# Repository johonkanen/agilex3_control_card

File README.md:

# Agilex 3 control card

A small FPGA control card built around an Altera Agilex 3 (A3CZ065BB18AE7S, B18A BGA), designed in KiCad 10. It plugs
into a power-electronics board through a 2×25 1.27 mm header and replaces an older Cyclone 10 card (U25) with the same
outline and connector positions.

| Top | Bottom |
|---|---|
|  |  |

**Status: ready to order (2026-10-28).** The design is complete and fully routed; DRC is clean and the board matches the
schematic. It passed three independent reviews (production files against JLCPCB's capabilities, electrical design, and the
Agilex 3 configuration against Altera's guidelines and two evaluation-kit schematics). After the reviews, the 1.2 V and
HyperRAM 1.8 V LDOs were replaced by bucks and all bucks set to forced PWM (`docs/power_switchers_plan.md`); that change
has not had a separate review. The FPGAs are being bought through
JLCPCB Global Sourcing; the assembly order follows when they reach JLC's warehouse. The board has not been built or tested
yet: `docs/bringup_checklist.md` is the plan for when it arrives.

## Features

- **FPGA:** Agilex 3 A3CZ065, 65k logic elements, speed grade −7, extended temperature. 63 I/O signals, mostly on 3.3 V HVIO
  banks with no level shifters.
- **Memory:** 32 MB HyperRAM (Winbond W958D8NBYA5I, 1.8 V) on bank 6D. The W959D8NFYA5I (64 MB) fits the same footprint.
- **Configuration:** Active Serial x4 from a 1.8 V QSPI flash (Micron MT25QU256). JTAG on a 5-pin 2.54 mm header,
  shifted from 3.3 V to 1.8 V by an SN74AVC4T774.
- **Clock:** 100 MHz 1.8 V oscillator into PLLREFCLK1 (D18) and the configuration clock input OSC_CLK_1.
- **ADC:** 2 channels, each an 8:1 analog mux (SN74LV4051A) → OPA365 buffer → ADS7056 (14-bit, 2.5 MSPS), on a separate
  analog 3.3 V supply.
- **Power:** from 5 V on the header. Every FPGA rail comes from a Diodes AP61x02 buck, all in forced PWM: 0.753 V core
  (with remote sense), 1.8 V, 3.3 V, then 1.2 V and a separate 1.8 V for the HyperRAM bank. They start up in Altera's
  group order, each step enabled by the previous buck's power-good. Only the analog 3.3 V comes from an LDO. The FPGA's
  PLL, ADC and VCCRCORE supplies are filtered with ferrite beads.
- **Indicators:** 2 RGB LEDs.
- **Board:** 32.5 × 33.8 mm, 6 layers, 1.6 mm (JLC stackup JLC06161H-3313), ENIG, 0.65 mm-pitch BGA fanned out with
  filled and capped via-in-pad. 161 parts assembled by JLCPCB on both sides (40 top, 121 bottom); the headers J1 and J2
  are soldered by hand.

## Copper layers

<!-- board-plots:start -->
<!-- Generated by kicad-board-plots; edits between these markers are overwritten. -->

Copper layers of `hardware/control_card.kicad_pcb` in stack order, without silkscreen. Plotted by [kicad-board-plots](https://github.com/johonkanen/kicad-board-plots) on each board change; the images live on the `renders` branch.

<table>
<tr>
<td align="center"><br><b>F.Cu: signal (top)</b></td>
<td align="center"><br><b>In1.Cu: GND plane</b></td>
</tr>
<tr>
<td align="center"><br><b>In2.Cu: signal, +1V8, +1V8_HR, +1V2 pours</b></td>
<td align="center"><br><b>In3.Cu: +0V75, +3V3 planes</b></td>
</tr>
<tr>
<td align="center"><br><b>In4.Cu: GND plane</b></td>
<td align="center"><br><b>B.Cu: signal, GND, +1V2, SW_3V3, SW_1V2, SW_1V8HR and 7 more pours (bottom, mirrored)</b></td>
</tr>
</table>

<!-- board-plots:end -->

## Repository layout

| Path | Contents |
|---|---|
| `hardware/` | KiCad project: schematic (`control_card.kicad_sch` plus `sheets/`), board, design rules (`control_card.kicad_dru` adds JLCPCB limits) |
| `hardware/lib/` | Project symbols and footprints, including the Agilex 3 symbol and the B18A BGA footprint |
| `reference/` | FPGA pin assignment (`pin_assignment.csv`), Altera pin lists, power-board header pinout, JLCPCB part list |
| `docs/` | Design notes, Agilex 3 board requirements, flash requirements, production and bring-up checklists, board renders |
| `tools/` | Python scripts that generated the schematic and board, plus the fabrication-output wrapper |
| `tools/jlc/` | Submodule [jlc-tools](https://github.com/johonkanen/jlc-tools): JLC part search, stock check, BOM/CPL and Gerber export |

## Documentation

- [`docs/design-notes.md`](docs/design-notes.md): architecture, part choices and the reasons for them.
- [`docs/agilex3_requirements.md`](docs/agilex3_requirements.md): what the FPGA needs from the board (supply rails,
  bank voltages, power-up order, configuration pins) and how this card meets each requirement.
- [`docs/agilex_flash_requirements.md`](docs/agilex_flash_requirements.md): configuration flash requirements.
- [`docs/jlcpcb_production_checklist.md`](docs/jlcpcb_production_checklist.md): verifying the design and order files
  against JLCPCB's capabilities, plus the order-form settings.
- [`docs/bringup_checklist.md`](docs/bringup_checklist.md): testing the assembled boards, from inspection and first
  power-up to configuration, HyperRAM, ADCs and the power-board interface.
- [`docs/order_checklist.md`](docs/order_checklist.md): the earlier hand-off list from routing to ordering (history).

## Opening the design

Clone with `git clone --recursive`, or run `git submodule update --init` after cloning, to get `tools/jlc`.

Open `hardware/control_card.kicad_pro` in KiCad 10. The project's own symbol and footprint libraries are set up in
`hardware/sym-lib-table` and `hardware/fp-lib-table`. Everything else comes from KiCad's standard libraries.

## Fabrication outputs

```sh
KICAD_ROOT=<unpacked KiCad AppImage (squashfs-root)> tools/fab_outputs.sh
```

This writes `hardware/fab/`:
- Gerbers and drill files, zipped;
- the JLCPCB BOM and placement files;
- a DRC report.

The headers J1 and J2 are left out of the assembly files, because they are soldered by hand. The FPGA has no JLCPCB
part number, so order it through JLCPCB's Global Sourcing or supply it yourself. Global Sourcing parts can only be used
in an assembly order once they have arrived in JLC's warehouse (Parts Manager → My Parts Lib).

Check stock right before ordering: judge each part by JLC's orderable quantity and minimum purchase, not the plain stock
count (see the production checklist, section 5):

```sh
python3 -I tools/jlc/stock_check.py hardware/fab/bom_jlcpcb.csv --boards 10
```

## FPGA pin assignment

`reference/pin_assignment.csv` lists every used FPGA ball with its signal, bank, direction and pin function, generated
from the schematic netlist. Quartus settings:
- banks 6C and 6D: 1.8-V LVCMOS;
- other banks: 3.3-V LVCMOS;
- configuration scheme: Active Serial x4;
- `DEVICE_INITIALIZATION_CLOCK OSC_CLK_1_100MHZ`;
- `ACTIVE_SERIAL_CLOCK AS_FREQ_100MHZ`.

## Generator scripts

The initial schematic and board came from the scripts in `tools/`:
- `gen_schematic.py` writes the schematic;
- `build_pcb.sh` builds the board: placement, FPGA pin assignment, power copper and routing.

The design has since been edited by hand in KiCad, so **don't rerun `gen_schematic.py` or `build_pcb.sh` on this
version**: they would overwrite the hand edits, pin swaps and routing. They stay in the repository as a record of how
the design was made.

## License

[MIT](LICENSE).

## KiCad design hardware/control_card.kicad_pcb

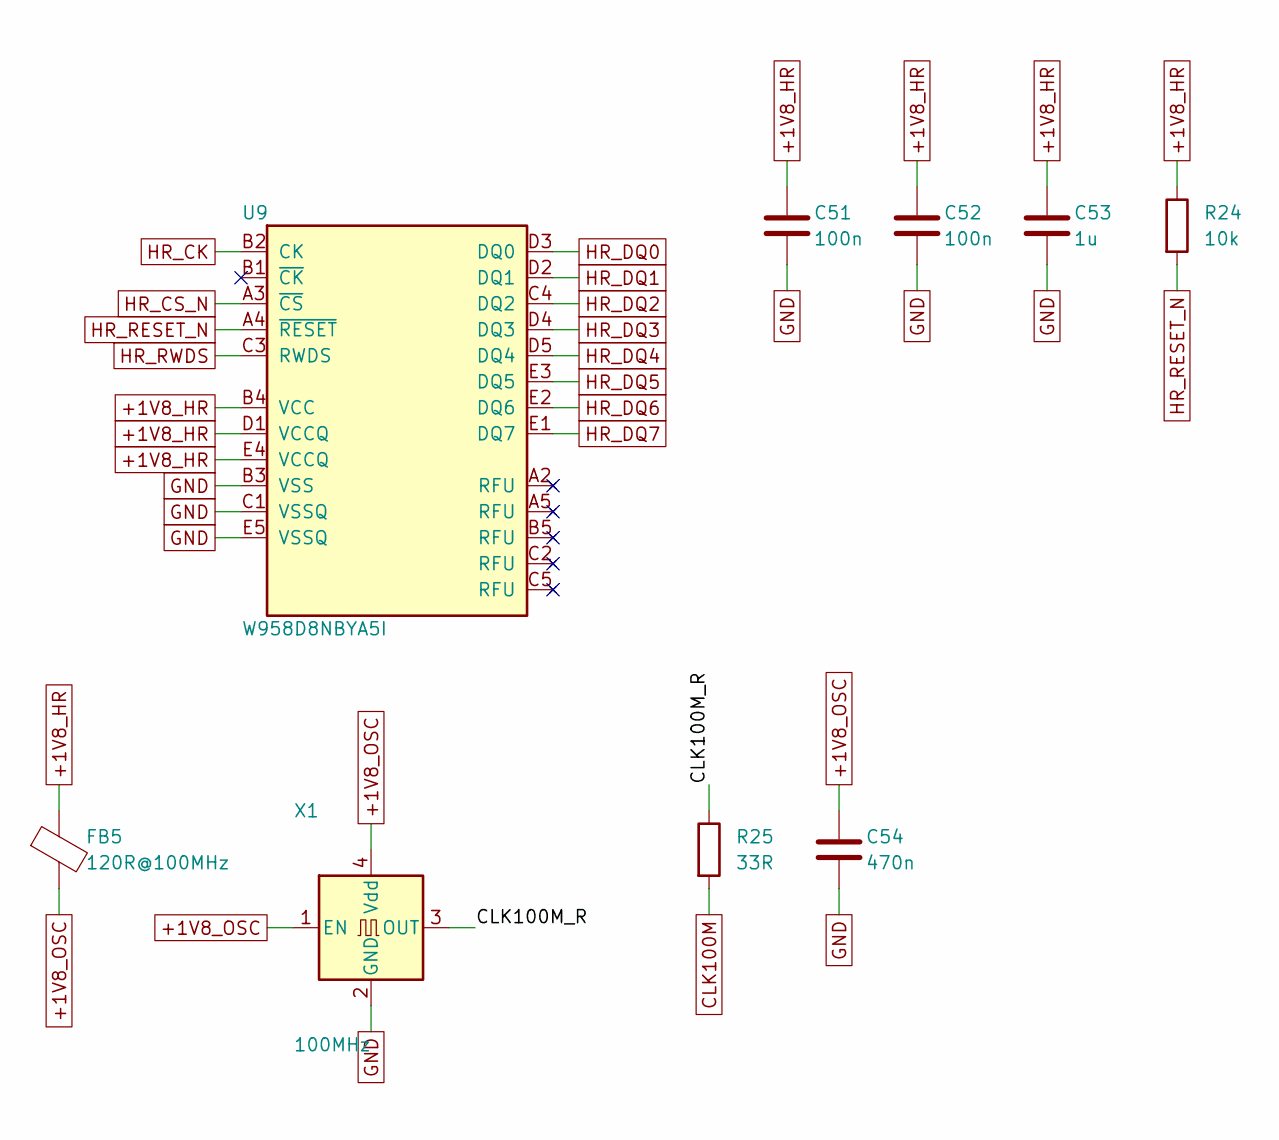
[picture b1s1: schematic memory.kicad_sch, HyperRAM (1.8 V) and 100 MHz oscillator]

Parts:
C51, C52: 100n; C_0402_1005Metric; MPN CL05B104KO5NNNC; LCSC C1525
C53: 1u; C_0402_1005Metric; MPN CL05A105KA5NQNC; LCSC C52923
C54: 470n; C_0402_1005Metric; MPN CL05A474KP5NNNC; LCSC C47339
FB5: 120R@100MHz; L_0603_1608Metric; MPN BLM18PG121SN1D; LCSC C14709
R24: 10k; R_0402_1005Metric; MPN 0402WGF1002TCE; LCSC C25744
R25: 33R; R_0402_1005Metric; MPN 0402WGF330JTCE; LCSC C25105
U9: W958D8NBYA5I; BGA-24_6x8mm_Layout5x5_P1.0mm_CY0.5; MPN W958D8NBYA5I; LCSC C7420405
X1: 100MHz; Oscillator_SMD_Abracon_ASE-4Pin_3.2x2.5mm; MPN OT3225100MJBA4SL; LCSC C4353707

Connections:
+1V8_HR: C51.1, C52.1, C53.1, FB5.1, R24.1, U9.B4 (VCC), U9.D1 (VCCQ), U9.E4 (VCCQ); also elsewhere on the board
+1V8_OSC: C54.1, FB5.2, X1.1 (EN), X1.4 (Vdd)
/HyperRAM and clock/CLK100M_R: R25.1, X1.3 (OUT)
CLK100M: R25.2; also elsewhere on the board
GND: C51.2, C52.2, C53.2, C54.2, U9.B3 (VSS), U9.C1 (VSSQ), U9.E5 (VSSQ), X1.2 (GND); also elsewhere on the board
HR_CK: U9.B2 (CK); also elsewhere on the board
HR_CS_N: U9.A3 (~CS); also elsewhere on the board
HR_DQ0: U9.D3 (DQ0); also elsewhere on the board
HR_DQ1: U9.D2 (DQ1); also elsewhere on the board
HR_DQ2: U9.C4 (DQ2); also elsewhere on the board
HR_DQ3: U9.D4 (DQ3); also elsewhere on the board
HR_DQ4: U9.D5 (DQ4); also elsewhere on the board
HR_DQ5: U9.E3 (DQ5); also elsewhere on the board
HR_DQ6: U9.E2 (DQ6); also elsewhere on the board
HR_DQ7: U9.E1 (DQ7); also elsewhere on the board
HR_RESET_N: R24.2, U9.A4 (~RESET); also elsewhere on the board
HR_RWDS: U9.C3 (RWDS); also elsewhere on the board

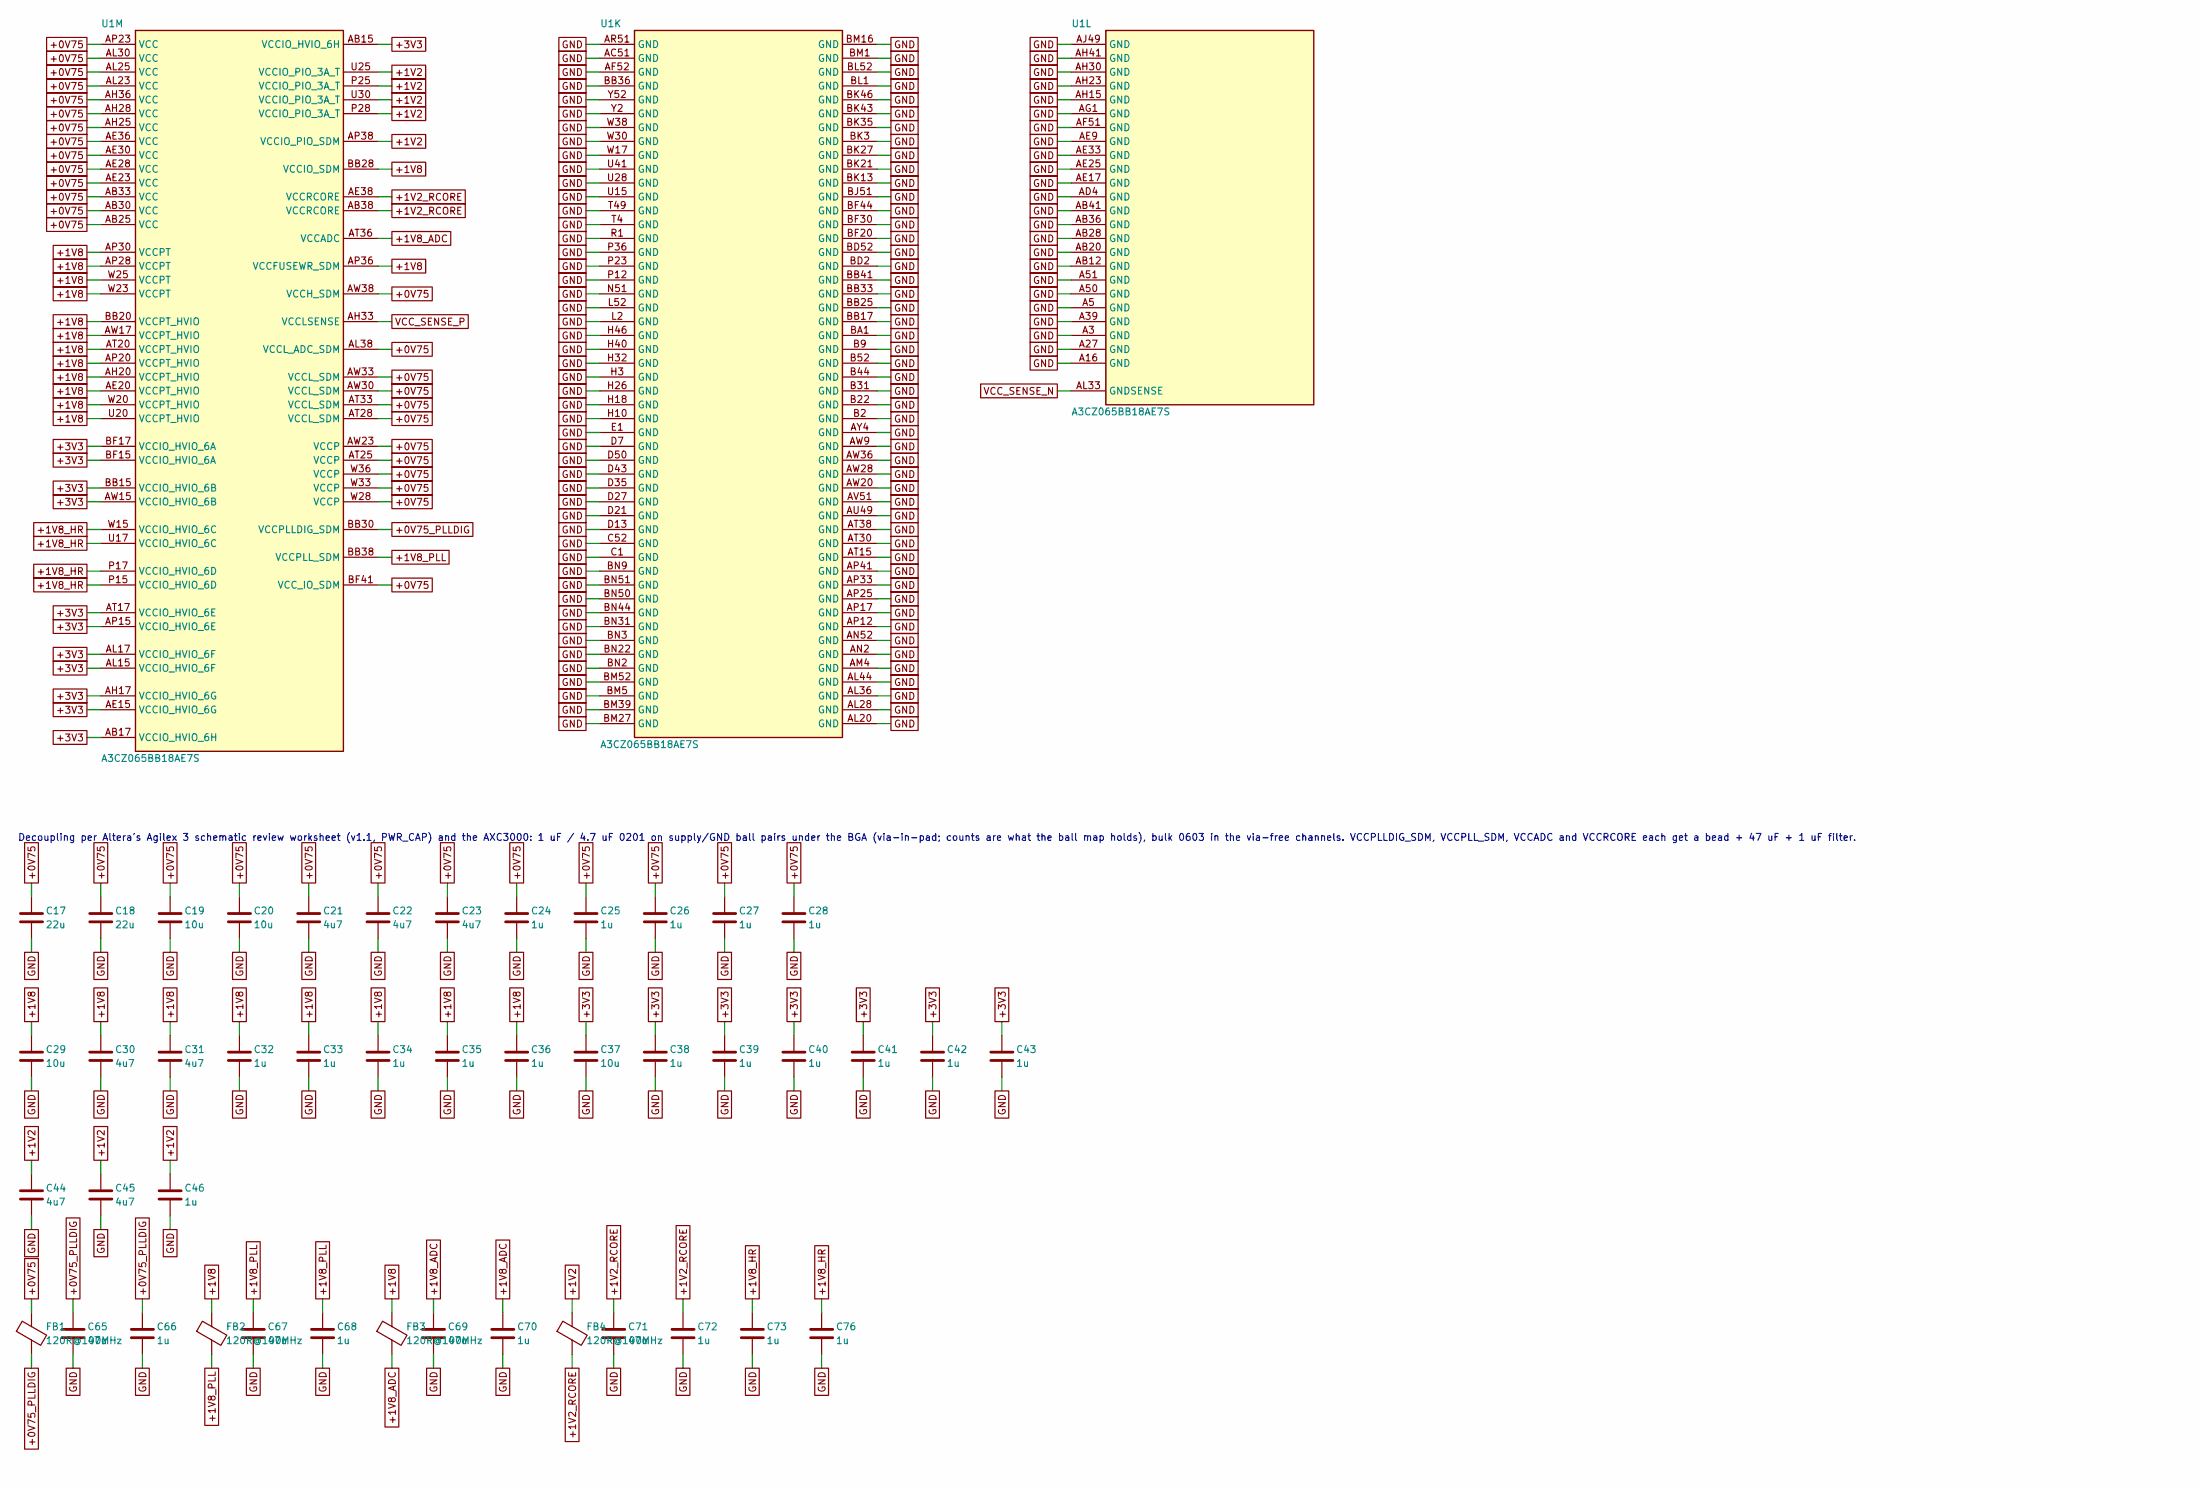
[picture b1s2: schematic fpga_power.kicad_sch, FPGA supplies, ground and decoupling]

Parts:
C17, C18: 22u; C_0603_1608Metric; MPN CL10A226MQ8NRNC; LCSC C59461
C19, C20, C29, C37: 10u; C_0603_1608Metric; MPN CL10A106KP8NNNC; LCSC C19702
C21, C22, C23, C30, C31, C45: 4u7; C_0201_0603Metric; MPN JDK063BBJ475MV-AT; LCSC C2880368
C24, C25, C26, C27, C28, C32, C33, C34, C35, C36, C38, C39, C40, C41, C42, C43, C46, C66, C68, C70, C72, C73, C76: 1u; C_0201_0603Metric; MPN CL03A105MQ3CSNC; LCSC C170152
C44: 4u7; C_0603_1608Metric; MPN CL10A475KO8NNNC; LCSC C19666
C65, C67, C69, C71: 47u; C_0603_1608Metric; MPN GRM188R60J476ME15D; LCSC C140782
FB1, FB2, FB3, FB4: 120R@100MHz; L_0603_1608Metric; MPN BLM18PG121SN1D; LCSC C14709
U1: A3CZ065BB18AE7S; Altera_B18A; MPN A3CZ065BB18AE7S

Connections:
+0V75: C17.1, C18.1, C19.1, C20.1, C21.1, C22.1, C23.1, C24.1, C25.1, C26.1, C27.1, C28.1, FB1.1, U1.AB25 (VCC), U1.AB30 (VCC), U1.AB33 (VCC), U1.AE23 (VCC), U1.AE28 (VCC), U1.AE30 (VCC), U1.AE36 (VCC), U1.AH25 (VCC), U1.AH28 (VCC), U1.AH36 (VCC), U1.AL23 (VCC), U1.AL25 (VCC), U1.AL30 (VCC), U1.AL38 (VCCL_ADC_SDM), U1.AP23 (VCC), U1.AT25 (VCCP), U1.AT28 (VCCL_SDM), U1.AT33 (VCCL_SDM), U1.AW23 (VCCP), U1.AW30 (VCCL_SDM), U1.AW33 (VCCL_SDM), U1.AW38 (VCCH_SDM), U1.BF41 (VCC_IO_SDM), U1.W28 (VCCP), U1.W33 (VCCP), U1.W36 (VCCP); also elsewhere on the board
+0V75_PLLDIG: C65.1, C66.1, FB1.2, U1.BB30 (VCCPLLDIG_SDM)
+1V2: C44.1, C45.1, C46.1, FB4.1, U1.AP38 (VCCIO_PIO_SDM), U1.P25 (VCCIO_PIO_3A_T), U1.P28 (VCCIO_PIO_3A_T), U1.U25 (VCCIO_PIO_3A_T), U1.U30 (VCCIO_PIO_3A_T); also elsewhere on the board
+1V2_RCORE: C71.1, C72.1, FB4.2, U1.AB38 (VCCRCORE), U1.AE38 (VCCRCORE)
+1V8: C29.1, C30.1, C31.1, C32.1, C33.1, C34.1, C35.1, C36.1, FB2.1, FB3.1, U1.AE20 (VCCPT_HVIO), U1.AH20 (VCCPT_HVIO), U1.AP20 (VCCPT_HVIO), U1.AP28 (VCCPT), U1.AP30 (VCCPT), U1.AP36 (VCCFUSEWR_SDM), U1.AT20 (VCCPT_HVIO), U1.AW17 (VCCPT_HVIO), U1.BB20 (VCCPT_HVIO), U1.BB28 (VCCIO_SDM), U1.U20 (VCCPT_HVIO), U1.W20 (VCCPT_HVIO), U1.W23 (VCCPT), U1.W25 (VCCPT); also elsewhere on the board
+1V8_ADC: C69.1, C70.1, FB3.2, U1.AT36 (VCCADC)
+1V8_HR: C73.1, C76.1, U1.P15 (VCCIO_HVIO_6D), U1.P17 (VCCIO_HVIO_6D), U1.U17 (VCCIO_HVIO_6C), U1.W15 (VCCIO_HVIO_6C); also elsewhere on the board
+1V8_PLL: C67.1, C68.1, FB2.2, U1.BB38 (VCCPLL_SDM)
+3V3: C37.1, C38.1, C39.1, C40.1, C41.1, C42.1, C43.1, U1.AB15 (VCCIO_HVIO_6H), U1.AB17 (VCCIO_HVIO_6H), U1.AE15 (VCCIO_HVIO_6G), U1.AH17 (VCCIO_HVIO_6G), U1.AL15 (VCCIO_HVIO_6F), U1.AL17 (VCCIO_HVIO_6F), U1.AP15 (VCCIO_HVIO_6E), U1.AT17 (VCCIO_HVIO_6E), U1.AW15 (VCCIO_HVIO_6B), U1.BB15 (VCCIO_HVIO_6B), U1.BF15 (VCCIO_HVIO_6A), U1.BF17 (VCCIO_HVIO_6A); also elsewhere on the board
GND: C17.2, C18.2, C19.2, C20.2, C21.2, C22.2, C23.2, C24.2, C25.2, C26.2, C27.2, C28.2, C29.2, C30.2, C31.2, C32.2, C33.2, C34.2, C35.2, C36.2, C37.2, C38.2, C39.2, C40.2, C41.2, C42.2, C43.2, C44.2, C45.2, C46.2, C65.2, C66.2, C67.2, C68.2, C69.2, C70.2, C71.2, C72.2, C73.2, C76.2, U1.A3 (GND), U1.A5 (GND), U1.A16 (GND), U1.A27 (GND), U1.A39 (GND), U1.A50 (GND), U1.A51 (GND), U1.AB12 (GND), U1.AB20 (GND), U1.AB28 (GND), U1.AB36 (GND), U1.AB41 (GND), U1.AC51 (GND), U1.AD4 (GND), U1.AE9 (GND), U1.AE17 (GND), U1.AE25 (GND), U1.AE33 (GND), U1.AF51 (GND), U1.AF52 (GND), U1.AG1 (GND), U1.AH15 (GND), U1.AH23 (GND), U1.AH30 (GND), U1.AH41 (GND), U1.AJ49 (GND), U1.AL20 (GND), U1.AL28 (GND), U1.AL36 (GND), U1.AL44 (GND), U1.AM4 (GND), U1.AN2 (GND), U1.AN52 (GND), U1.AP12 (GND), U1.AP17 (GND), U1.AP25 (GND), U1.AP33 (GND), U1.AP41 (GND), U1.AR51 (GND), U1.AT15 (GND), U1.AT30 (GND), U1.AT38 (GND), U1.AU49 (GND), U1.AV51 (GND), U1.AW9 (GND), U1.AW20 (GND), U1.AW28 (GND), U1.AW36 (GND), U1.AY4 (GND), U1.B2 (GND), U1.B9 (GND), U1.B22 (GND), U1.B31 (GND), U1.B44 (GND), U1.B52 (GND), U1.BA1 (GND), U1.BB17 (GND), U1.BB25 (GND), U1.BB33 (GND), U1.BB36 (GND), U1.BB41 (GND), U1.BD2 (GND), U1.BD52 (GND), U1.BF20 (GND), U1.BF30 (GND), U1.BF44 (GND), U1.BJ51 (GND), U1.BK3 (GND), U1.BK13 (GND), U1.BK21 (GND), U1.BK27 (GND), U1.BK35 (GND), U1.BK43 (GND), U1.BK46 (GND), U1.BL1 (GND), U1.BL52 (GND), U1.BM1 (GND), U1.BM5 (GND), U1.BM16 (GND), U1.BM27 (GND), U1.BM39 (GND), U1.BM52 (GND), U1.BN2 (GND), U1.BN3 (GND), U1.BN9 (GND), U1.BN22 (GND), U1.BN31 (GND), U1.BN44 (GND), U1.BN50 (GND), U1.BN51 (GND), U1.C1 (GND), U1.C52 (GND), U1.D7 (GND), U1.D13 (GND), U1.D21 (GND), U1.D27 (GND), U1.D35 (GND), U1.D43 (GND), U1.D50 (GND), U1.E1 (GND), U1.H3 (GND), U1.H10 (GND), U1.H18 (GND), U1.H26 (GND), U1.H32 (GND), U1.H40 (GND), U1.H46 (GND), U1.L2 (GND), U1.L52 (GND), U1.N51 (GND), U1.P12 (GND), U1.P23 (GND), U1.P36 (GND), U1.R1 (GND), U1.T4 (GND), U1.T49 (GND), U1.U15 (GND), U1.U28 (GND), U1.U41 (GND), U1.W17 (GND), U1.W30 (GND), U1.W38 (GND), U1.Y2 (GND), U1.Y52 (GND); also elsewhere on the board
VCC_SENSE_N: U1.AL33 (GNDSENSE); also elsewhere on the board
VCC_SENSE_P: U1.AH33 (VCCLSENSE); also elsewhere on the board

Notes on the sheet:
Decoupling per Altera's Agilex 3 schematic review worksheet (v1.1, PWR_CAP) and the AXC3000: 1 uF / 4.7 uF 0201 on supply/GND ball pairs under the BGA (via-in-pad; counts are what the ball map holds), bulk 0603 in the via-free channels. VCCPLLDIG_SDM, VCCPLL_SDM, VCCADC and VCCRCORE each get a bead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

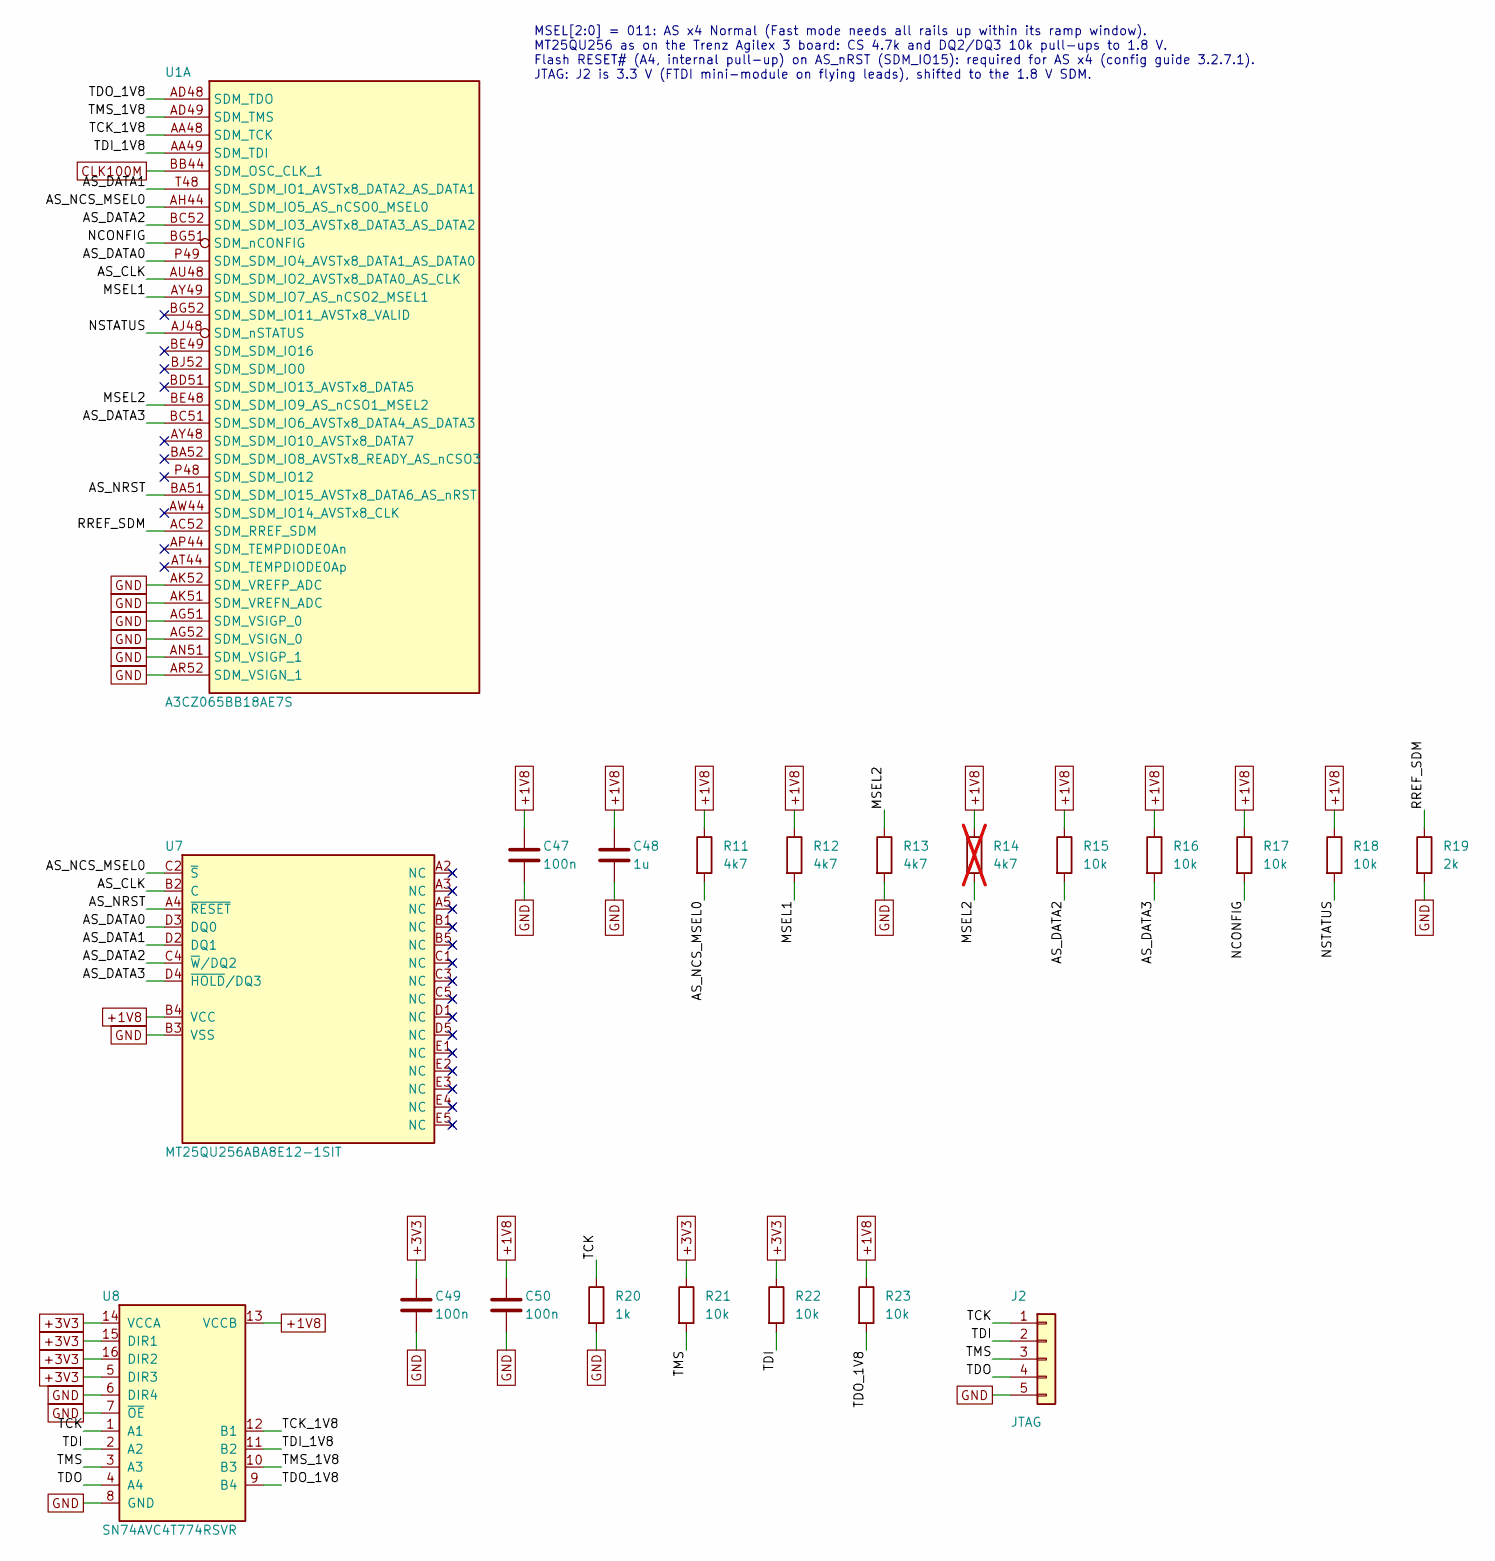
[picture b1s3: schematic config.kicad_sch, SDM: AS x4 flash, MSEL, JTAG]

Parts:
C47: 100n; C_0402_1005Metric; MPN CL05B104KO5NNNC; LCSC C1525
C48: 1u; C_0402_1005Metric; MPN CL05A105KA5NQNC; LCSC C52923
C49, C50: 100n; C_0201_0603Metric; MPN CL03A104KP3NNNC; LCSC C49062
J2: JTAG; PinHeader_1x05_P2.54mm_Vertical
R11, R12, R13: 4k7; R_0402_1005Metric; MPN 0402WGF4701TCE; LCSC C25900
R14: 4k7; R_0402_1005Metric; MPN 0402WGF4701TCE; LCSC C25900; not fitted
R15, R16, R17, R18: 10k; R_0402_1005Metric; MPN 0402WGF1002TCE; LCSC C25744
R19: 2k; R_0402_1005Metric; MPN 0402WGF2001TCE; LCSC C4109
R20: 1k; R_0201_0603Metric; MPN 0201WMF1001TEE; LCSC C270365
R21, R22, R23: 10k; R_0201_0603Metric; MPN 0201WMF1002TEE; LCSC C473048
U1: A3CZ065BB18AE7S; Altera_B18A; MPN A3CZ065BB18AE7S
U7: MT25QU256ABA8E12-1SIT; BGA-24_6x8mm_Layout5x5_P1.0mm_CY0.5; MPN MT25QU256ABA8E12-1SIT; LCSC C2061023
U8: SN74AVC4T774RSVR; UQFN-16_1.8x2.6mm_P0.4mm; MPN SN74AVC4T774RSVR; LCSC C779392

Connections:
+1V8: C47.1, C48.1, C50.1, R11.1, R12.1, R14.1, R15.1, R16.1, R17.1, R18.1, R23.1, U7.B4 (VCC), U8.13 (VCCB); also elsewhere on the board
+3V3: C49.1, R21.1, R22.1, U8.5 (DIR3), U8.14 (VCCA), U8.15 (DIR1), U8.16 (DIR2); also elsewhere on the board
/Configuration/AS_CLK: U1.AU48 (SDM_SDM_IO2_AVSTx8_DATA0_AS_CLK), U7.B2 (C)
/Configuration/AS_DATA0: U1.P49 (SDM_SDM_IO4_AVSTx8_DATA1_AS_DATA0), U7.D3 (DQ0)
/Configuration/AS_DATA1: U1.T48 (SDM_SDM_IO1_AVSTx8_DATA2_AS_DATA1), U7.D2 (DQ1)
/Configuration/AS_DATA2: R15.2, U1.BC52 (SDM_SDM_IO3_AVSTx8_DATA3_AS_DATA2), U7.C4 (~W/DQ2)
/Configuration/AS_DATA3: R16.2, U1.BC51 (SDM_SDM_IO6_AVSTx8_DATA4_AS_DATA3), U7.D4 (~HOLD/DQ3)
/Configuration/AS_NCS_MSEL0: R11.2, U1.AH44 (SDM_SDM_IO5_AS_nCSO0_MSEL0), U7.C2 (~S)
/Configuration/AS_NRST: U1.BA51 (SDM_SDM_IO15_AVSTx8_DATA6_AS_nRST), U7.A4 (~RESET)
/Configuration/MSEL1: R12.2, U1.AY49 (SDM_SDM_IO7_AS_nCSO2_MSEL1)
/Configuration/MSEL2: R13.1, R14.2, U1.BE48 (SDM_SDM_IO9_AS_nCSO1_MSEL2)
/Configuration/NCONFIG: R17.2, U1.BG51 (SDM_nCONFIG)
/Configuration/NSTATUS: R18.2, U1.AJ48 (SDM_nSTATUS)
/Configuration/RREF_SDM: R19.1, U1.AC52 (SDM_RREF_SDM)
/Configuration/TCK: J2.1, R20.1, U8.1 (A1)
/Configuration/TCK_1V8: U1.AA48 (SDM_TCK), U8.12 (B1)
/Configuration/TDI: J2.2, R22.2, U8.2 (A2)
/Configuration/TDI_1V8: U1.AA49 (SDM_TDI), U8.11 (B2)
/Configuration/TDO: J2.4, U8.4 (A4)
/Configuration/TDO_1V8: R23.2, U1.AD48 (SDM_TDO), U8.9 (B4)
/Configuration/TMS: J2.3, R21.2, U8.3 (A3)
/Configuration/TMS_1V8: U1.AD49 (SDM_TMS), U8.10 (B3)
CLK100M: U1.BB44 (SDM_OSC_CLK_1); also elsewhere on the board
GND: C47.2, C48.2, C49.2, C50.2, J2.5, R13.2, R19.2, R20.2, U1.AG51 (SDM_VSIGP_0), U1.AG52 (SDM_VSIGN_0), U1.AK51 (SDM_VREFN_ADC), U1.AK52 (SDM_VREFP_ADC), U1.AN51 (SDM_VSIGP_1), U1.AR52 (SDM_VSIGN_1), U7.B3 (VSS), U8.6 (DIR4), U8.7 (~OE), U8.8 (GND); also elsewhere on the board

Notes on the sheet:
MSEL[2:0] = 011: AS x4 Normal (Fast mode needs all rails up within its ramp window). MT25QU256 as on the Trenz Agilex 3 board: CS 4.7k and DQ2/DQ3 10k pull-ups to 1.8 V. Flash RESET# (A4, internal pull-up) on AS_nRST (SDM_IO15): required for AS x4 (config guide 3.2.7.1). JTAG: J2 is 3.3 V (FTDI min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

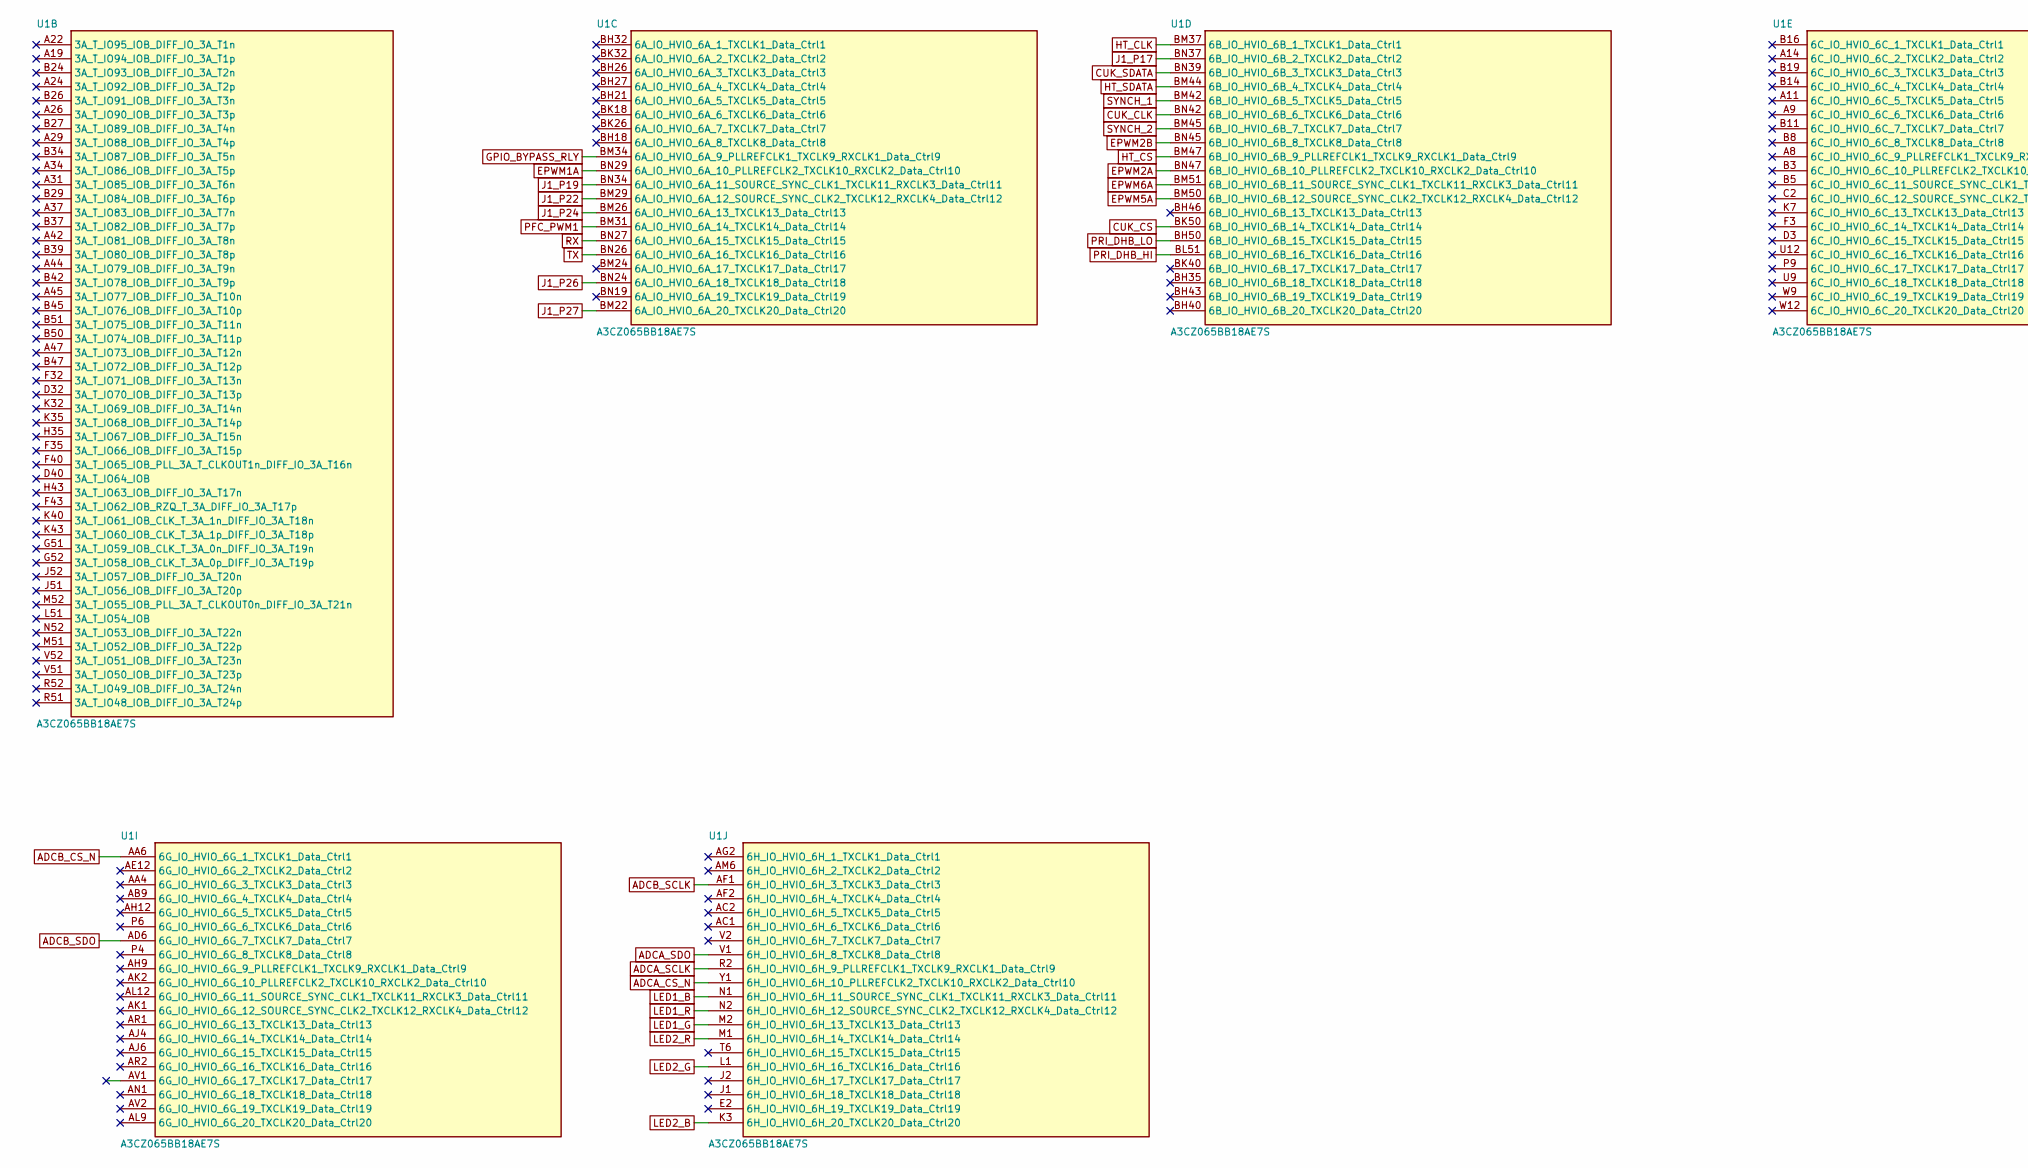
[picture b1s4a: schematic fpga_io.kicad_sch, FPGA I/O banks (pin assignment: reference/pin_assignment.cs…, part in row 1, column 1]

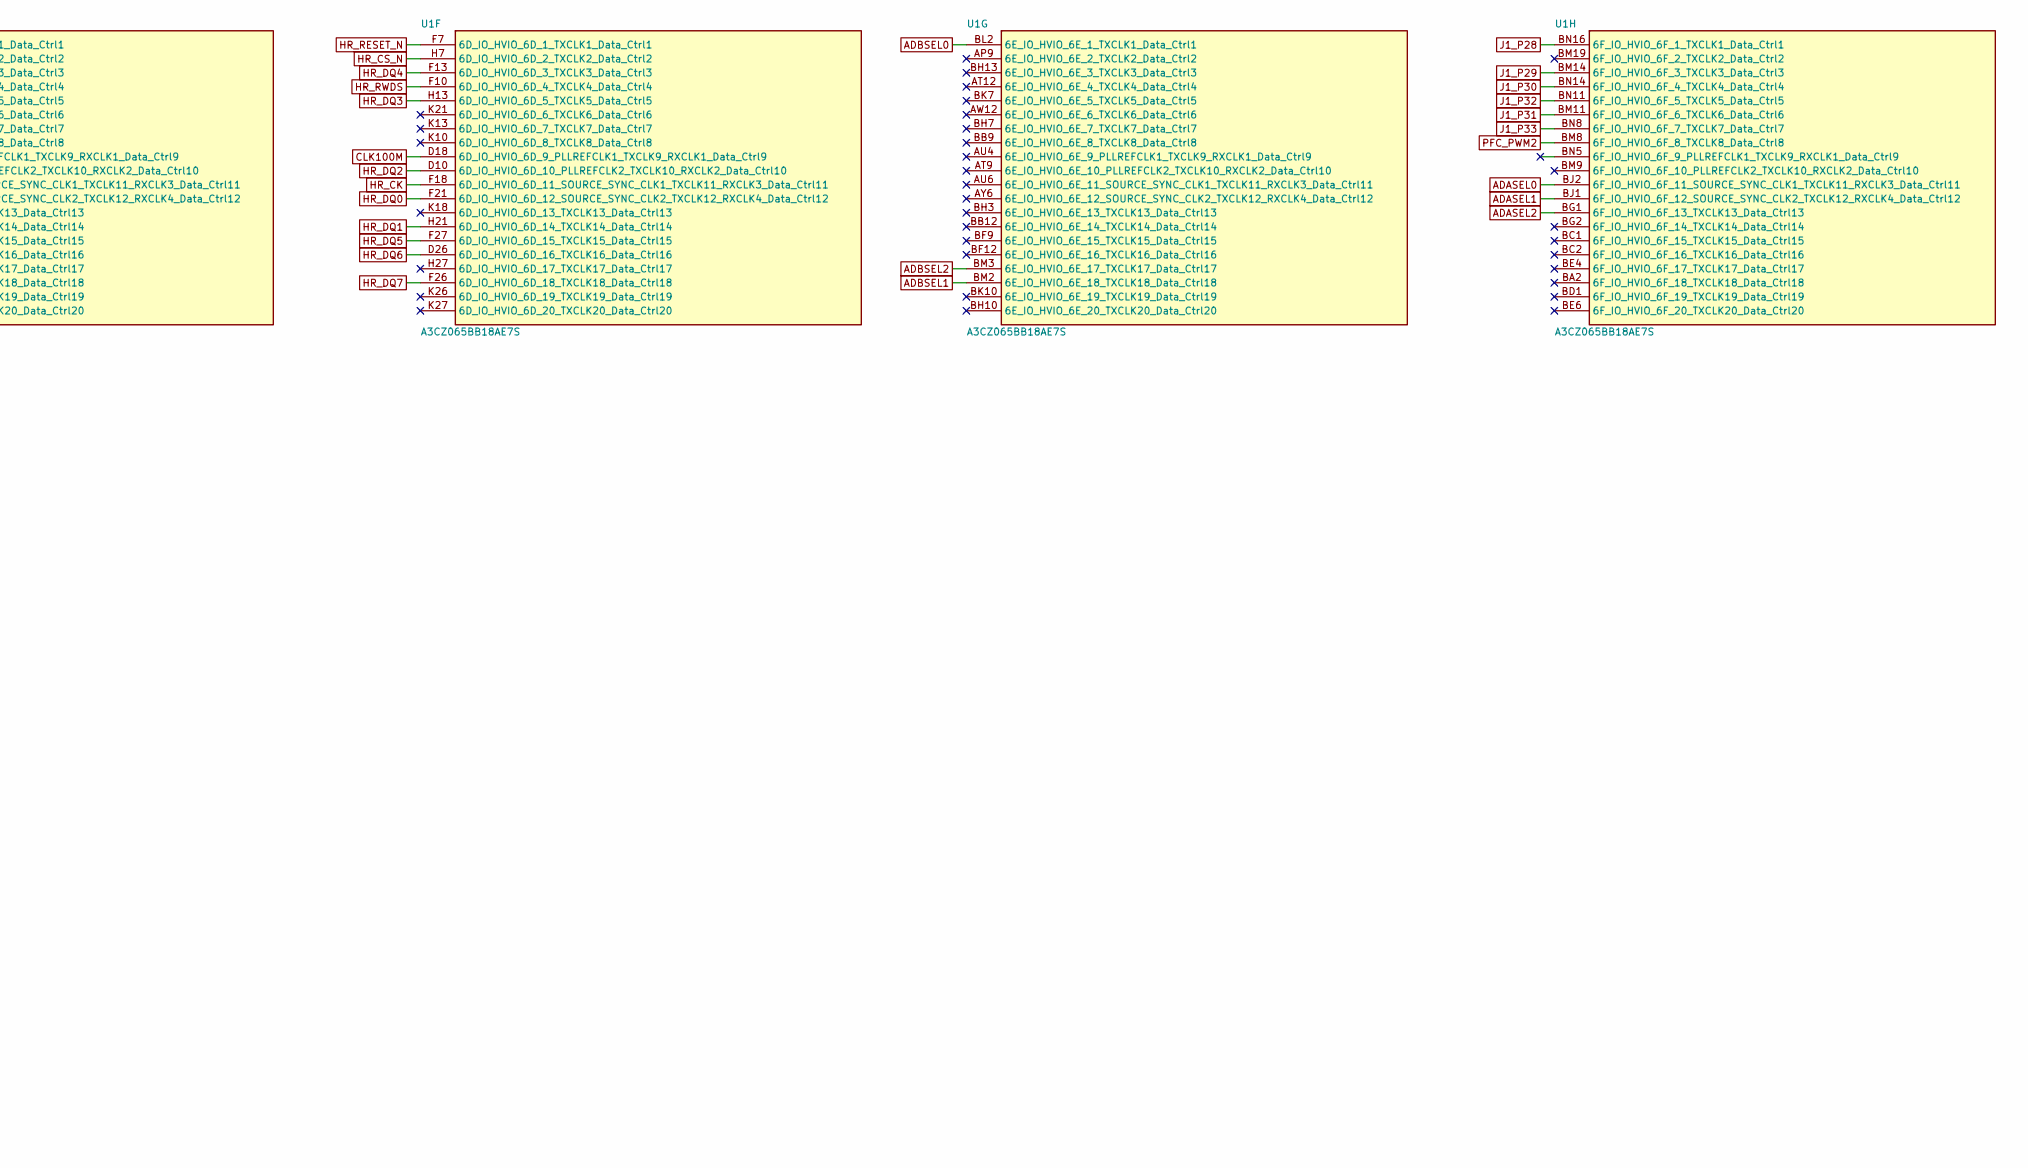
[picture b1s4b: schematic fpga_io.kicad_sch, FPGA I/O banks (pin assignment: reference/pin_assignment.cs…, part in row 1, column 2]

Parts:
U1: A3CZ065BB18AE7S; Altera_B18A; MPN A3CZ065BB18AE7S

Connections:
ADASEL0: U1.BJ2 (6F_IO_HVIO_6F_11_SOURCE_SYNC_CLK1_TXCLK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); also elsewhere on the board
ADASEL1: U1.BJ1 (6F_IO_HVIO_6F_12_SOURCE_SYNC_CLK2_TXCLK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); also elsewhere on the board
ADASEL2: U1.BG1 (6F_IO_HVIO_6F_13_TXCLK13_Data_Ctrl13); also elsewhere on the board
ADBSEL0: U1.BL2 (6E_IO_HVIO_6E_1_TXCLK1_Data_Ctrl1); also elsewhere on the board
ADBSEL1: U1.BM2 (6E_IO_HVIO_6E_18_TXCLK18_Data_Ctrl18); also elsewhere on the board
ADBSEL2: U1.BM3 (6E_IO_HVIO_6E_17_TXCLK17_Data_Ctrl17); also elsewhere on the board
ADCA_CS_N: U1.Y1 (6H_IO_HVIO_6H_10_PLLREFCLK2_TXCLK10_RXC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); also elsewhere on the board
ADCA_SCLK: U1.R2 (6H_IO_HVIO_6H_9_PLLREFCLK1_TXCLK9_RXCLK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); also elsewhere on the board
ADCA_SDO: U1.V1 (6H_IO_HVIO_6H_8_TXCLK8_Data_Ctrl8); also elsewhere on the board
ADCB_CS_N: U1.AA6 (6G_IO_HVIO_6G_1_TXCLK1_Data_Ctrl1); also elsewhere on the board
ADCB_SCLK: U1.AF1 (6H_IO_HVIO_6H_3_TXCLK3_Data_Ctrl3); also elsewhere on the board
ADCB_SDO: U1.AD6 (6G_IO_HVIO_6G_7_TXCLK7_Data_Ctrl7); also elsewhere on the board
CLK100M: U1.D18 (6D_IO_HVIO_6D_9_PLLREFCLK1_TXCLK9_RXCLK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); also elsewhere on the board
CUK_CLK: U1.BN42 (6B_IO_HVIO_6B_6_TXCLK6_Data_Ctrl6); also elsewhere on the board
CUK_CS: U1.BK50 (6B_IO_HVIO_6B_14_TXCLK14_Data_Ctrl14); also elsewhere on the board
CUK_SDATA: U1.BN39 (6B_IO_HVIO_6B_3_TXCLK3_Data_Ctrl3); also elsewhere on the board
EPWM1A: U1.BN29 (6A_IO_HVIO_6A_10_PLLREFCLK2_TXCLK10_RXC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); also elsewhere on the board
EPWM2A: U1.BN47 (6B_IO_HVIO_6B_10_PLLREFCLK2_TXCLK10_RXC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); also elsewhere on the board
EPWM2B: U1.BN45 (6B_IO_HVIO_6B_8_TXCLK8_Data_Ctrl8); also elsewhere on the board
EPWM5A: U1.BM50 (6B_IO_HVIO_6B_12_SOURCE_SYNC_CLK2_TXCLK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); also elsewhere on the board
EPWM6A: U1.BM51 (6B_IO_HVIO_6B_11_SOURCE_SYNC_CLK1_TXCLK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); also elsewhere on the board
GPIO_BYPASS_RLY: U1.BM34 (6A_IO_HVIO_6A_9_PLLREFCLK1_TXCLK9_RXCLK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); also elsewhere on the board
HR_CK: U1.F18 (6D_IO_HVIO_6D_11_SOURCE_SYNC_CLK1_TXCLK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); also elsewhere on the board
HR_CS_N: U1.H7 (6D_IO_HVIO_6D_2_TXCLK2_Data_Ctrl2); also elsewhere on the board
HR_DQ0: U1.F21 (6D_IO_HVIO_6D_12_SOURCE_SYNC_CLK2_TXCLK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); also elsewhere on the board
HR_DQ1: U1.H21 (6D_IO_HVIO_6D_14_TXCLK14_Data_Ctrl14); also elsewhere on the board
HR_DQ2: U1.D10 (6D_IO_HVIO_6D_10_PLLREFCLK2_TXCLK10_RXC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); also elsewhere on the board
HR_DQ3: U1.H13 (6D_IO_HVIO_6D_5_TXCLK5_Data_Ctrl5); also elsewhere on the board
HR_DQ4: U1.F13 (6D_IO_HVIO_6D_3_TXCLK3_Data_Ctrl3); also elsewhere on the board
HR_DQ5: U1.F27 (6D_IO_HVIO_6D_15_TXCLK15_Data_Ctrl15); also elsewhere on the board
HR_DQ6: U1.D26 (6D_IO_HVIO_6D_16_TXCLK16_Data_Ctrl16); also elsewhere on the board
HR_DQ7: U1.F26 (6D_IO_HVIO_6D_18_TXCLK18_Data_Ctrl18); also elsewhere on the board
HR_RESET_N: U1.F7 (6D_IO_HVIO_6D_1_TXCLK1_Data_Ctrl1); also elsewhere on the board
HR_RWDS: U1.F10 (6D_IO_HVIO_6D_4_TXCLK4_Data_Ctrl4); also elsewhere on the board
HT_CLK: U1.BM37 (6B_IO_HVIO_6B_1_TXCLK1_Data_Ctrl1); also elsewhere on the board
HT_CS: U1.BM47 (6B_IO_HVIO_6B_9_PLLREFCLK1_TXCLK9_RXCLK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); also elsewhere on the board
HT_SDATA: U1.BM44 (6B_IO_HVIO_6B_4_TXCLK4_Data_Ctrl4); also elsewhere on the board
J1_P17: U1.BN37 (6B_IO_HVIO_6B_2_TXCLK2_Data_Ctrl2); also elsewhere on the board
J1_P19: U1.BN34 (6A_IO_HVIO_6A_11_SOURCE_SYNC_CLK1_TXCLK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); also elsewhere on the board
J1_P22: U1.BM29 (6A_IO_HVIO_6A_12_SOURCE_SYNC_CLK2_TXCLK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); also elsewhere on the board
J1_P24: U1.BM26 (6A_IO_HVIO_6A_13_TXCLK13_Data_Ctrl13); also elsewhere on the board
J1_P26: U1.BN24 (6A_IO_HVIO_6A_18_TXCLK18_Data_Ctrl18); also elsewhere on the board
J1_P27: U1.BM22 (6A_IO_HVIO_6A_20_TXCLK20_Data_Ctrl20); also elsewhere on the board
J1_P28: U1.BN16 (6F_IO_HVIO_6F_1_TXCLK1_Data_Ctrl1); also elsewhere on the board
J1_P29: U1.BM14 (6F_IO_HVIO_6F_3_TXCLK3_Data_Ctrl3); also elsewhere on the board
J1_P30: U1.BN14 (6F_IO_HVIO_6F_4_TXCLK4_Data_Ctrl4); also elsewhere on the board
J1_P31: U1.BM11 (6F_IO_HVIO_6F_6_TXCLK6_Data_Ctrl6); also elsewhere on the board
J1_P32: U1.BN11 (6F_IO_HVIO_6F_5_TXCLK5_Data_Ctrl5); also elsewhere on the board
J1_P33: U1.BN8 (6F_IO_HVIO_6F_7_TXCLK7_Data_Ctrl7); also elsewhere on the board
LED1_B: U1.N1 (6H_IO_HVIO_6H_11_SOURCE_SYNC_CLK1_TXCLK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); also elsewhere on the board
LED1_G: U1.M2 (6H_IO_HVIO_6H_13_TXCLK13_Data_Ctrl13); also elsewhere on the board
LED1_R: U1.N2 (6H_IO_HVIO_6H_12_SOURCE_SYNC_CLK2_TXCLK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); also elsewhere on the board
LED2_B: U1.K3 (6H_IO_HVIO_6H_20_TXCLK20_Data_Ctrl20); also elsewhere on the board
LED2_G: U1.L1 (6H_IO_HVIO_6H_16_TXCLK16_Data_Ctrl16); also elsewhere on the board
LED2_R: U1.M1 (6H_IO_HVIO_6H_14_TXCLK14_Data_Ctrl14); also elsewhere on the board
PFC_PWM1: U1.BM31 (6A_IO_HVIO_6A_14_TXCLK14_Data_Ctrl14); also elsewhere on the board
PFC_PWM2: U1.BM8 (6F_IO_HVIO_6F_8_TXCLK8_Data_Ctrl8); also elsewhere on the board
PRI_DHB_HI: U1.BL51 (6B_IO_HVIO_6B_16_TXCLK16_Data_Ctrl16); also elsewhere on the board
PRI_DHB_LO: U1.BH50 (6B_IO_HVIO_6B_15_TXCLK15_Data_Ctrl15); also elsewhere on the board
RX: U1.BN27 (6A_IO_HVIO_6A_15_TXCLK15_Data_Ctrl15); also elsewhere on the board
SYNCH_1: U1.BM42 (6B_IO_HVIO_6B_5_TXCLK5_Data_Ctrl5); also elsewhere on the board
SYNCH_2: U1.BM45 (6B_IO_HVIO_6B_7_TXCLK7_Data_Ctrl7); also elsewhere on the board
TX: U1.BN26 (6A_IO_HVIO_6A_16_TXCLK16_Data_Ctrl16); also elsewhere on the board
